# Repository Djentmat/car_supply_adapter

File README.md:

# car_supply_adapter
Car supply adapter scheme with using 7805

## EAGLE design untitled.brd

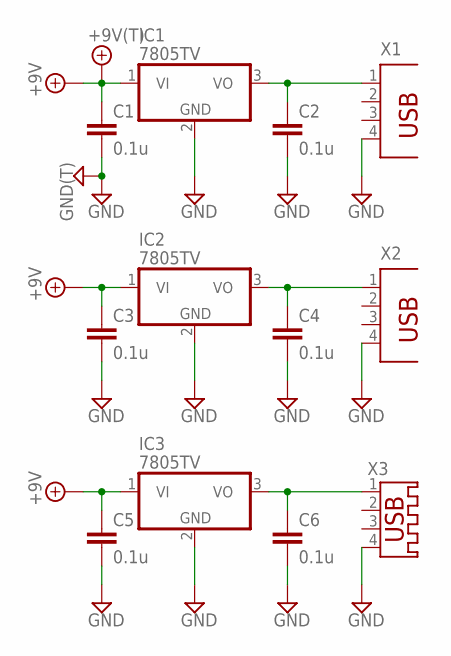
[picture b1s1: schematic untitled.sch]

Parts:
+9V1: +9V(T); SQUARE
C1, C2, C3, C4, C5, C6: 0.1u; 075X035_4
GND1: GND(T); SQUARE
IC1, IC2, IC3: 7805TV; TO220V
X1, X2: PN87520
X3: USB-A003

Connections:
+9V: +9V1.1, C1.1, C3.1, C5.1, IC1.1 (VI), IC2.1 (VI), IC3.1 (VI)
GND: C1.2, C2.2, C3.2, C4.2, C5.2, C6.2, GND1.1, IC1.2 (GND), IC2.2 (GND), IC3.2 (GND), X1.4, X2.4, X3.4
unnamed: C2.1, IC1.3 (VO), X1.1
unnamed: C4.1, IC2.3 (VO), X2.1
unnamed: C6.1, IC3.3 (VO), X3.1

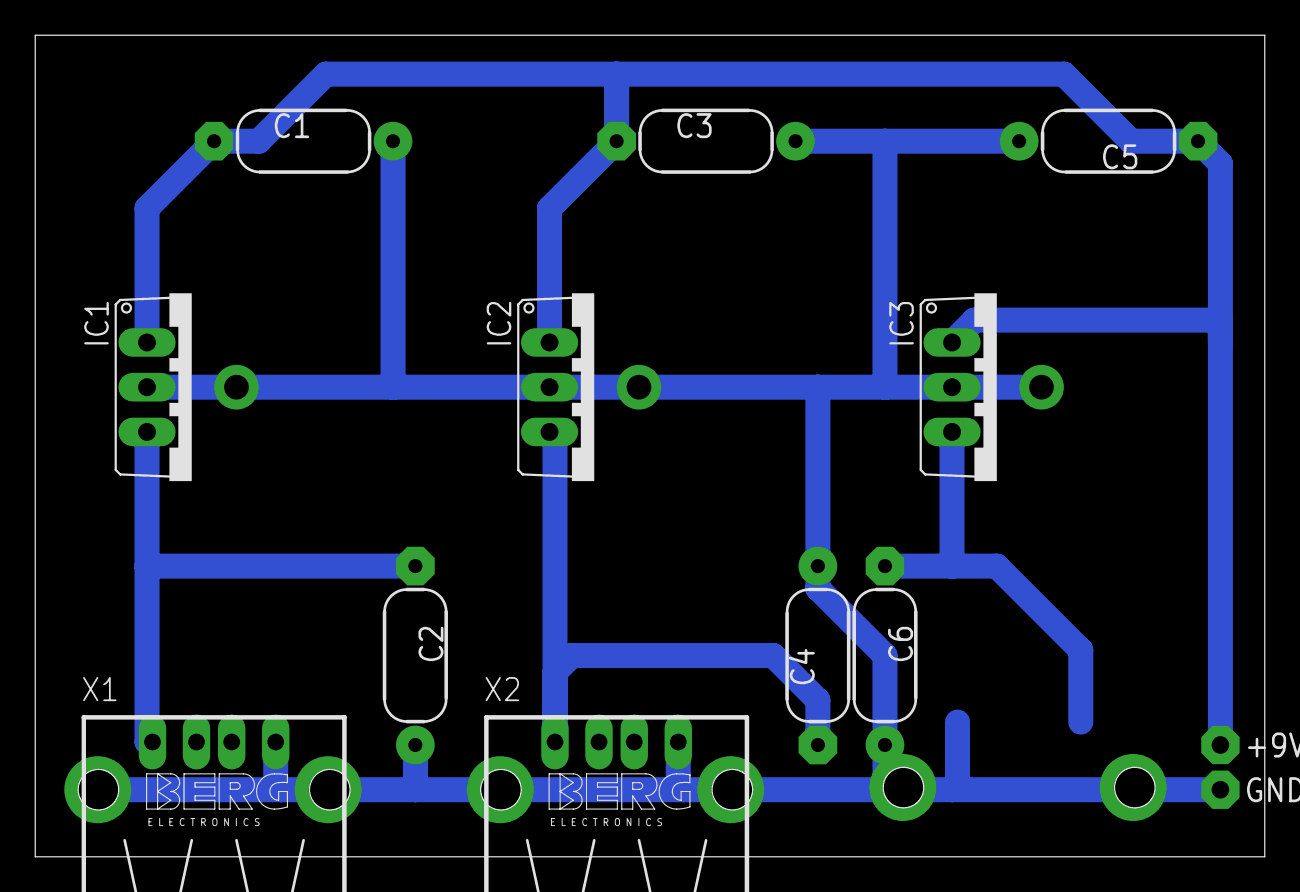
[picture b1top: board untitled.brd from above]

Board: 2 copper layers, 69.8 x 46.7 mm, 14 parts (1 on the bottom side), 5 nets.
